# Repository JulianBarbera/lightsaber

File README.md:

# lightsaber
 Light stick project with a few added features

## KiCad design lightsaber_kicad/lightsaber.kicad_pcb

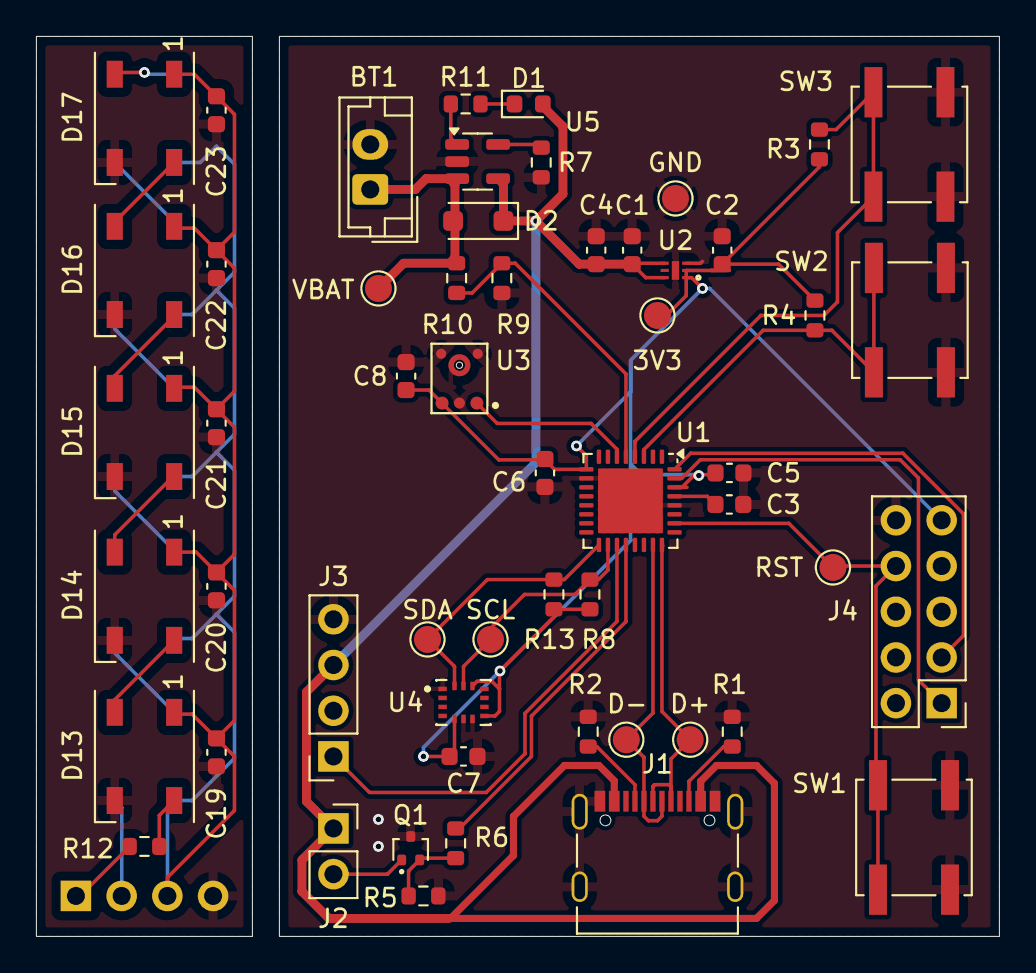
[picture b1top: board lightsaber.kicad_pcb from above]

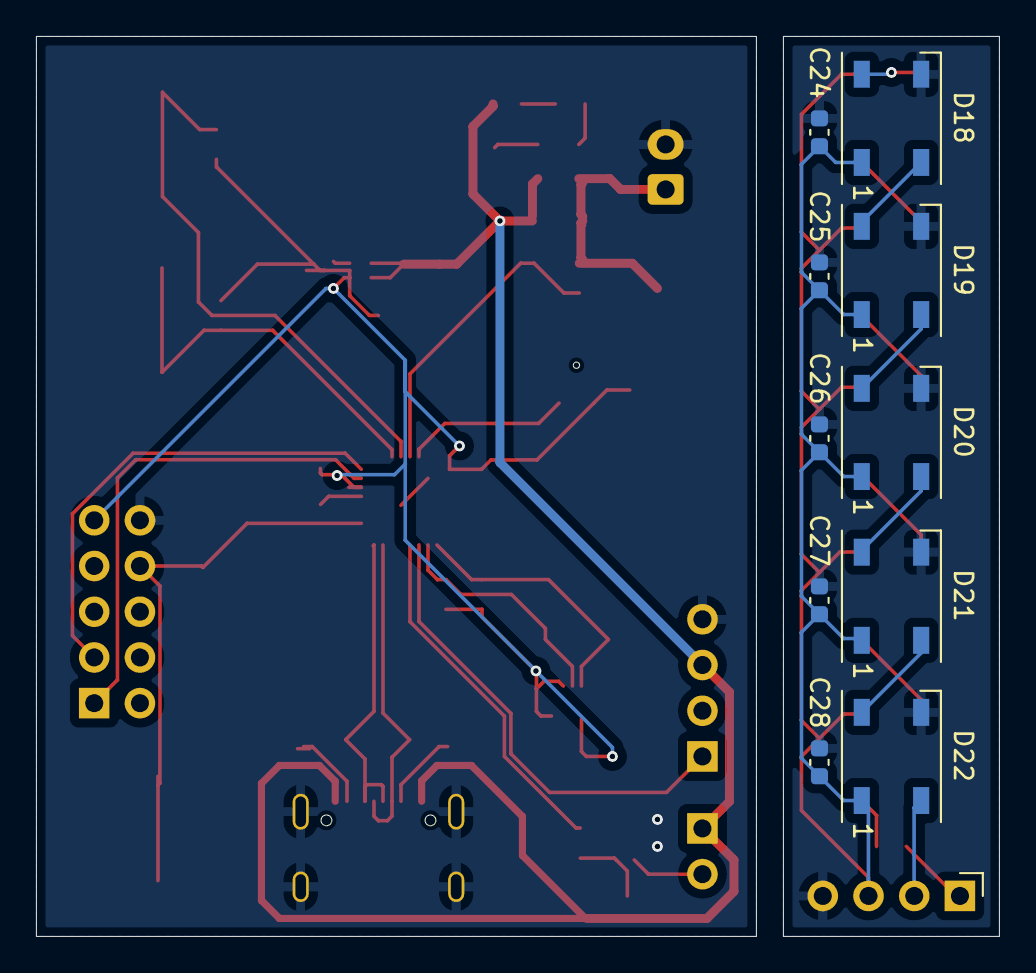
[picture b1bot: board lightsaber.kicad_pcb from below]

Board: 2 copper layers, 53.5 x 50.0 mm, 66 parts (11 on the bottom side), 38 nets.

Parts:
3V3: TP_3v3; TestPoint_Pad_D1.5mm
BT1: Battery; JST_EH_B2B-EH-A_1x02_P2.50mm_Vertical
C1, C2, C3, C19, C20, C21, C22, C23, C24, C25, C26, C27, C28: 1uF; C_0603_1608Metric
C4: 10uF; C_0603_1608Metric
C5, C6, C7, C8: 0.1uF; C_0603_1608Metric
D1: LED; LED_0603_1608Metric
D2: MBR120; D_SOD-123F
D13, D14, D15, D16, D17, D18, D19, D20, D21, D22: WS2812B; LED_WS2812B_PLCC4_5.0x5.0mm_P3.2mm
D+: TP_D-; TestPoint_Pad_D1.5mm
D-: TP_D+; TestPoint_Pad_D1.5mm
GND: TP_GND; TestPoint_Pad_D1.5mm
J1: USB_C_Receptacle_USB2.0_14P; USB_C_Receptacle_Palconn_UTC16-G
J2: Conn_01x02_Socket; PinSocket_1x02_P2.54mm_Vertical
J3: Conn_01x04_Socket; PinSocket_1x04_P2.54mm_Vertical
J4: JTAGICE3; PinHeader_2x05_P2.54mm_Vertical
J5: Conn_01x04_Pin; PinHeader_1x04_P2.54mm_Horizontal
Q1: NMOS; SOT-416
R1, R2, R11: 5.1k; R_0603_1608Metric
R3, R4, R5: 10k; R_0603_1608Metric
R6: 200; R_0603_1608Metric
R7: 2K; R_0603_1608Metric
R8, R13: 3.3k; R_0603_1608Metric
R9, R10: 100k; R_0603_1608Metric
R12: 300; R_0603_1608Metric
RST: TP_RESET; TestPoint_Pad_D1.5mm
SCL: TP_SCL; TestPoint_Pad_D1.5mm
SDA: TP_SDA; TestPoint_Pad_D1.5mm
SW1, SW2, SW3: SW_SPST; SW_Push_1P1T_NO_CK_KSC6xxJ
U1: ATSAMD21E17D-M; QFN-32-1EP_5x5mm_P0.5mm_EP3.6x3.6mm
U2: XDFN6_711AT_ONS-L
U3: XDCR_SPU0410LR5H-QB
U4: XDCR_ICM-42670-P
U5: MCP73831-2-OT; SOT-23-5
VBAT: TP_VBAT; TestPoint_Pad_D1.5mm

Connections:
+3V3: 3V3.1, C2.1, C5.1, C6.1, C7.1, C8.1, J4.9, R3.1, R4.1, R8.1, R13.1, U1.9 (VDDANA), U1.30 (VDDIN), U2.1 (OUT), U2.2 (FB), U3.4 (VDD), U4.5 (VDDIO), U4.8 (VDD), U4.12 (AP_CS)
/BATT_SENSE: R9.1, R10.2, U1.5 (PA04)
/BUTTON_1: R4.2, SW2.1 (A), U1.3 (PA02)
/BUTTON_2: R3.2, SW3.1 (A), U1.4 (PA03)
/D+: D+.1, J1.A6 (D+), J1.B6 (D+), U1.24 (PA25)
/D-: D-.1, J1.A7 (D-), J1.B7 (D-), U1.23 (PA24)
/LASER: R6.2, U1.20 (PA19)
/MIC: U1.6 (PA05), U3.1 (OUTPUT)
/NEO_OUT: J3.1, U1.19 (PA18)
/NeoStick/DIN: J5.1, R12.1
/NeoStick/DOUT: D22.2 (DOUT), J5.2
/RESET: J4.8, RST.1, SW1.1 (A), U1.26 (~RESET)
/SCL: R8.2, SCL.1, U1.18 (PA17), U4.13 (AP_SCL)
/SDA: R13.2, SDA.1, U1.17 (PA16), U4.14 (AP_SDA)
/SWDCLK: J4.1, U1.31 (PA30)
/SWDIO: J4.3, U1.32 (PA31)
GND: BT1.2 (-), C1.2, C2.2, C3.1, C4.2, C5.2, C6.2, C7.2, C8.2, C19.2, C20.2, C21.2, C22.2, C23.2, C24.2, C25.2, C26.2, C27.2, C28.2, D13.3 (VSS), D14.3 (VSS), D15.3 (VSS), D16.3 (VSS), D17.3 (VSS), D18.3 (VSS), D19.3 (VSS), D20.3 (VSS), D21.3 (VSS), D22.3 (VSS), GND.1, J1.A1 (GND), J1.A12 (GND), J1.B1 (GND), J1.B12 (GND), J1.S1 (SHIELD), J3.4, J4.10, J5.4, Q1.3 (S), R1.1, R2.2, R5.1, R7.1, R9.2, SW1.2 (B), SW2.2 (B), SW3.2 (B), U1.10 (GND), U1.28 (GND), U1.33 (EP), U2.3 (GND), U2.7 (PAD), U3.2 (GROUND), U3.3 (GROUND), U3.5 (GROUND), U3.6 (GROUND), U4.1 (AP_AD0), U4.6 (GND), U4.7 (FSYNC), U5.2 (V_{SS})
unnamed: D1.1 (K), R11.1
unnamed: D13.4 (DIN), R12.2
unnamed: D13.2 (DOUT), D14.4 (DIN)
unnamed: D14.2 (DOUT), D15.4 (DIN)
unnamed: D15.2 (DOUT), D16.4 (DIN)
unnamed: D16.2 (DOUT), D17.4 (DIN)
unnamed: D17.2 (DOUT), D18.4 (DIN)
unnamed: D18.2 (DOUT), D19.4 (DIN)
unnamed: D19.2 (DOUT), D20.4 (DIN)
unnamed: D20.2 (DOUT), D21.4 (DIN)
unnamed: D21.2 (DOUT), D22.4 (DIN)
unnamed: J1.A5 (CC1), R2.1
unnamed: J1.B5 (CC2), R1.2
unnamed: J2.2, Q1.1 (D)
unnamed: Q1.2 (G), R5.2, R6.1
unnamed: C3.2, U1.29 (VDDCORE)
unnamed: R7.2, U5.5 (PROG)
unnamed: R11.2, U5.1 (STAT)
VBAT: BT1.1 (+), D2.2 (A), R10.1, U5.3 (V_{BAT}), VBAT.1
VBUS: C1.1, C4.1, D1.2 (A), D2.1 (K), J1.A4 (VBUS), J1.A9 (VBUS), J1.B4 (VBUS), J1.B9 (VBUS), J2.1, J3.3, U2.4 (EN), U2.6 (IN), U5.4 (V_{DD})
VDD: C19.1, C20.1, C21.1, C22.1, C23.1, C24.1, C25.1, C26.1, C27.1, C28.1, D13.1 (VDD), D14.1 (VDD), D15.1 (VDD), D16.1 (VDD), D17.1 (VDD), D18.1 (VDD), D19.1 (VDD), D20.1 (VDD), D21.1 (VDD), D22.1 (VDD), J5.3
